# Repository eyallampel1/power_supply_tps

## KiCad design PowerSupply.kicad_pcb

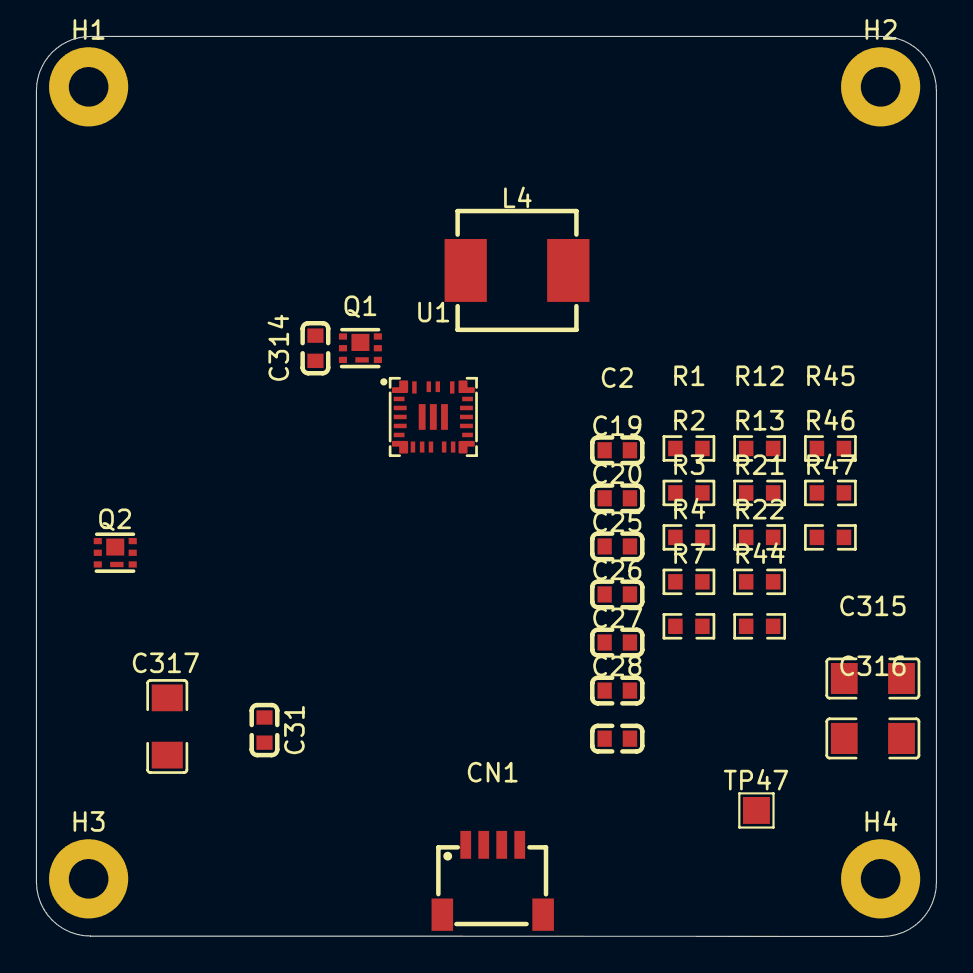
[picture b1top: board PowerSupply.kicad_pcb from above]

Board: 2 copper layers, 50.0 x 50.0 mm, 35 parts (0 on the bottom side), 25 nets, no tracks yet.

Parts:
C2, C19, C20: CC0603KRX7R9BB104; C0603
C25, C26: CL10A105KB8NNNC; C0603
C27: CC0603JRNPO9BN390; C0603
C28: CL10B222KB8NNNC; C0603
C31: CL10A475KO8NNNC; C0603
C314: CL10A226MO7JZNC; C0603
C315, C316, C317: CL31A226KAHNNNE; C1206
CN1: SM04B-SRSS-TB (LF)(SN); CONN-SMD_4P-P1.00_SM04B-SRSS-TB-LF-SN
H1, H2, H3, H4: MountingHole_Pad; MountingHole_2.2mm_M2_Pad
L4: CYA0630-4.7UH; IND-SMD_L7.2-W6.6_GPSR07X0
Q1, Q2: CSD17318Q2; WSON-6_L2.0-W2.0-P0.65-TL_CSD19538Q2
R1, R2: FRC0603J1R0 TS; R0603
R3, R4, R7, R12: RC0603JR-070RL; R0603
R13: RC0603FR-0749K9L; R0603
R21: CRCW060342K2FKEA; R0603
R22: RT0603BRD07113KL; R0603
R44, R45: 0603WAF1003T5E; R0603
R46: FRC0603F6041TS; R0603
R47: FRC0603F2213TS; R0603
TP47: TestPoint_Small; TestPoint_Pad_1.5x1.5mm
U1: TPS55288RPMR; VQFN-HR-26_L4.0-W3.5_TPS55288RPMR

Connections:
+5V: C26.2, C315.2, C316.2, C317.2, R3.2, R45.2, U1.13 (ISN)
/BOOT1: C2.1, U1.22 (BOOT1)
/BOOT2: C19.2, U1.20 (BOOT2)
/COMP_TPS: C27.2, C28.2, U1.18 (COMP)
/DITH: R7.2, U1.7 (DITH/SYNC)
/DR1H: R1.2, U1.2 (DR1H)
/DR1H_R: Q1.3 (G), R1.1
/DR1L: R2.1, U1.1 (DR1L)
/FB_TPS: R45.1, R46.2, U1.14 (FB/INT)
/FSW: R13.2, U1.8 (FSW)
/ILIM_TPS: R21.2, U1.17 (ILIM)
/PURPLE_CDC: R4.2, U1.16 (CDC)
/PURPLE_TPS_SCL: CN1.4, U1.5 (SCL)
/PURPLE_TPS_SDA: CN1.3, U1.6 (SDA)
/TPS_EN: C20.2, R44.2, R47.1, U1.4 (EN/UVLO)
/TPS_MODE_SEL: R12.2, U1.15 (MODE)
/TPS_SW1: C2.2, L4.1, Q1.4 (S), Q1.7 (S), Q2.1 (D), Q2.2 (D), Q2.5 (D), Q2.6 (D), Q2.8 (D), U1.23 (SW1)
/TPS_SW2: C19.1, L4.2, U1.21 (SW2), U1.25 (SW2)
/VCC_TPS: C31.1, U1.19 (VCC)
/VOUT_PURPLE_TPS: R3.1, U1.11 (VOUT), U1.12 (ISP), U1.26 (VOUT)
GND: CN1.1, H1.1, H2.1, H3.1, H4.1
GND_PURPLE: C20.1, C25.1, C26.1, C27.1, C31.2, C314.1, C315.1, C316.1, C317.1, Q2.4 (S), Q2.7 (S), R4.1, R7.1, R12.1, R13.1, R21.1, R22.1, R44.1, R46.1, U1.9 (PGND), U1.10 (AGND), U1.24 (PGND)
unnamed: C28.1, R22.2
unnamed: Q2.3 (G), R2.2
VIN: C25.2, C314.2, Q1.1 (D), Q1.2 (D), Q1.5 (D), Q1.6 (D), Q1.8 (D), R47.2, TP47.1, U1.3 (VIN)

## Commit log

2025-10-15 Added to pcb
2025-10-15 Removed TP
2025-10-23 Add Drone Kicad project
